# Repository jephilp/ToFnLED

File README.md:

# ToFnLED
ToF sensor + RGBW LED

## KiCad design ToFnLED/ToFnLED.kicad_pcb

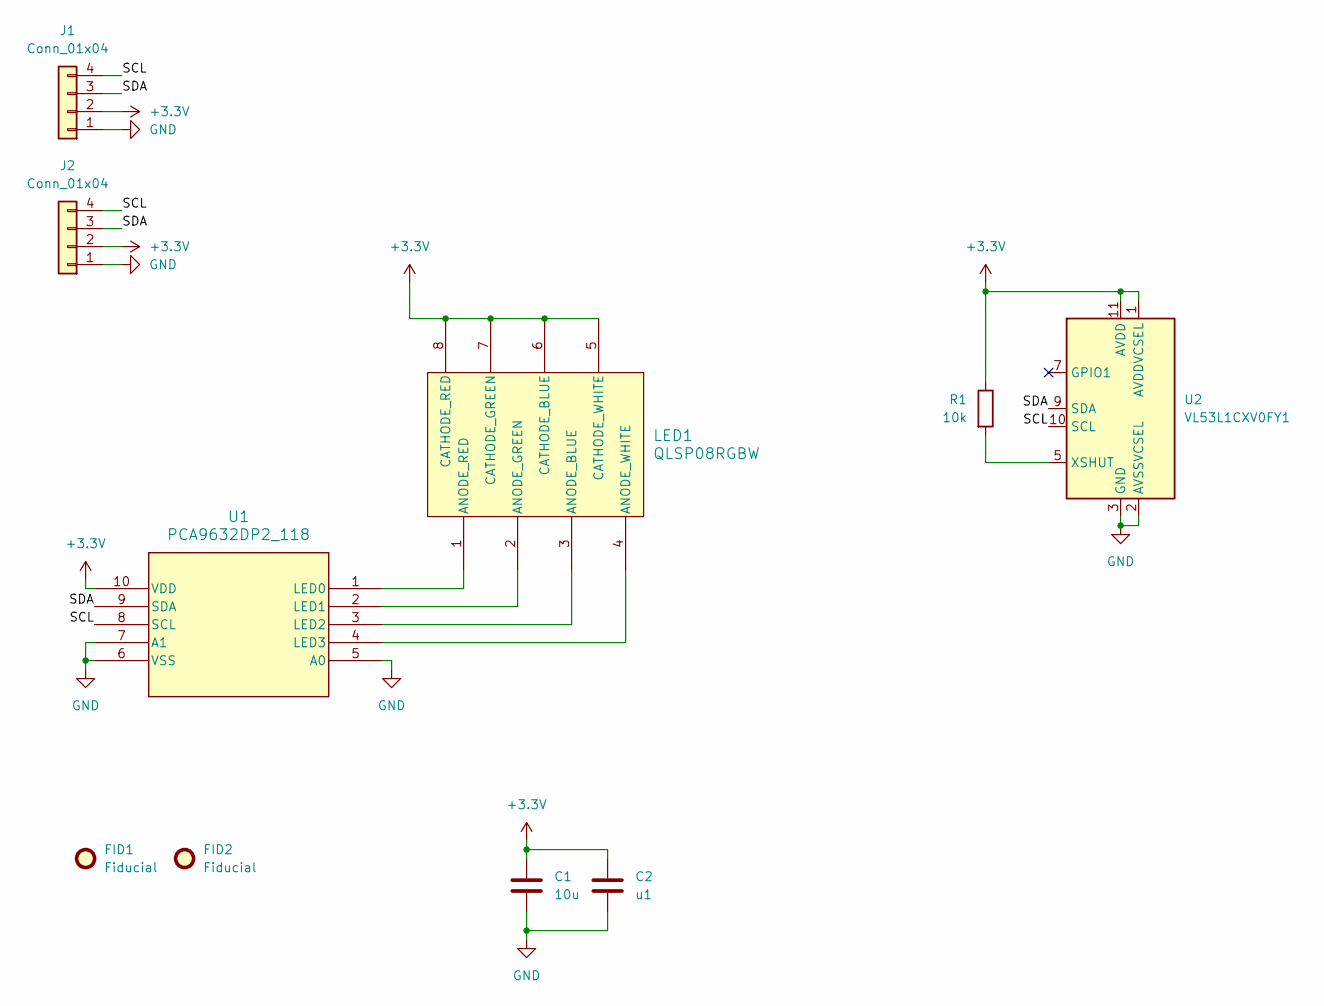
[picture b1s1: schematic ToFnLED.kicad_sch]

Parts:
C1: 10u; C_0805_2012Metric
C2: u1; C_0805_2012Metric
FID1, FID2: Fiducial; Fiducial_1mm_Mask2mm
J1: Conn_01x04; JST_SH_BM04B-SRSS-TB_1x04-1MP_P1.00mm_Vertical
J2: Conn_01x04; JST_SH_SM04B-SRSS-TB_1x04-1MP_P1.00mm_Horizontal
LED1: QLSP08RGBW; QLSP08RGBW_QUE
R1: 10k; R_0805_2012Metric
U1: PCA9632DP2_118; TSSOP10_3P1X3P1_NXP
U2: VL53L1CXV0FY1; ST_VL53L1x

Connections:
+3.3V: C1.1, C2.1, J1.2, J2.2, LED1.5 (CATHODE_WHITE), LED1.6 (CATHODE_BLUE), LED1.7 (CATHODE_GREEN), LED1.8 (CATHODE_RED), R1.1, U1.10 (VDD), U2.1 (AVDDVCSEL), U2.11 (AVDD)
/SCL: J1.4, J2.4, U1.8 (SCL), U2.10 (SCL)
/SDA: J1.3, J2.3, U1.9 (SDA), U2.9 (SDA)
GND: C1.2, C2.2, J1.1, J2.1, U1.5 (A0), U1.6 (VSS), U1.7 (A1), U2.2 (AVSSVCSEL), U2.3 (GND), U2.4 (GND), U2.6 (GND), U2.12 (GND)
unnamed: LED1.3 (ANODE_BLUE), U1.3 (LED2)
unnamed: LED1.2 (ANODE_GREEN), U1.2 (LED1)
unnamed: LED1.1 (ANODE_RED), U1.1 (LED0)
unnamed: LED1.4 (ANODE_WHITE), U1.4 (LED3)
unnamed: R1.2, U2.5 (XSHUT)

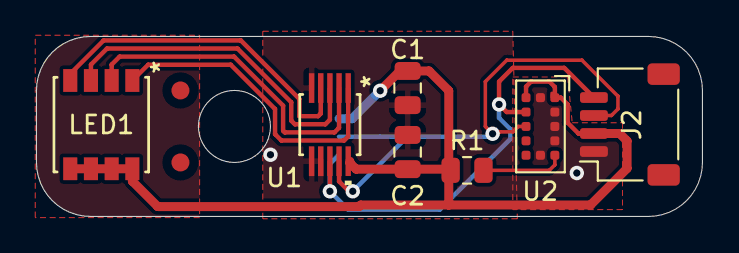
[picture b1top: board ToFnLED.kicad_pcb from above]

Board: 2 copper layers, 37.0 x 10.0 mm, 10 parts (1 on the bottom side), 9 nets.

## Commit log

2023-07-28 Updates
    Converted project to KiCAD, changed LED Driver to a PCA9632, and changed the LED to an RGBW one.
2023-07-30 Changed images
    Added images of schematic and top of board.
2023-07-30 Fixed images
    Wrong URL, corrected.
2023-07-30 Last README change
2023-07-30 Reversed LED connections
    Reversed LED connections to match that of Someluckys version of the ToFnLED.
2023-08-24 Small tweaks
